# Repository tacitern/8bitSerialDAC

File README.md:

# 8bitSerialDAC
An 8-bit DAC which uses a Shift Register and R-2R Ladder

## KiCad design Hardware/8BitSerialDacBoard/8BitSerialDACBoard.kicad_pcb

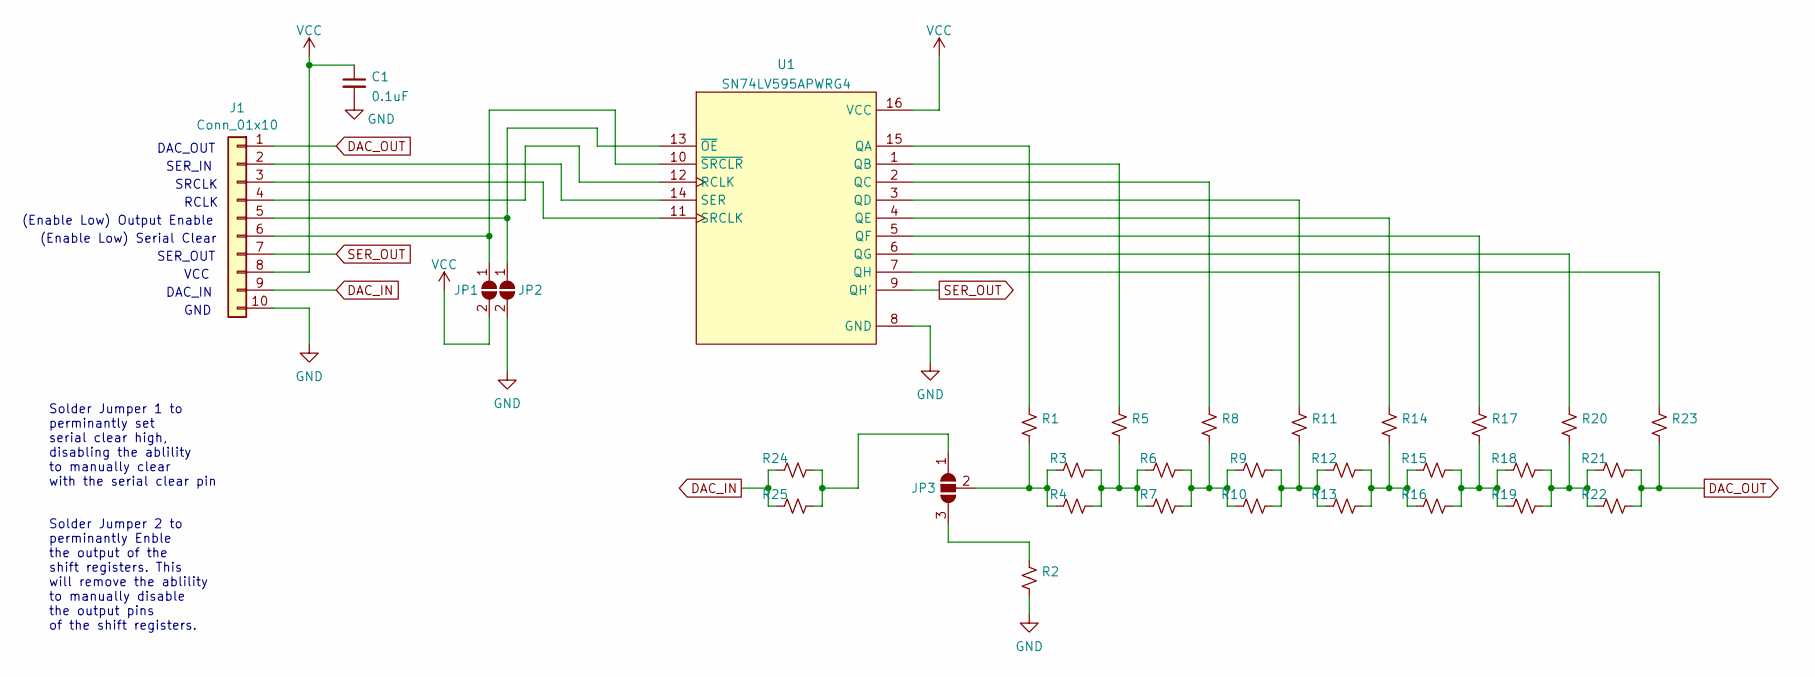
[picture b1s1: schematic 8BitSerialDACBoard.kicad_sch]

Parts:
C1: 0.1uF; C_0603_1608Metric_Pad1.08x0.95mm_HandSolder
J1: Conn_01x10; PinHeader_1x10_P2.54mm_Vertical
JP1, JP2: SolderJumper_2_Open; SolderJumper-2_P1.3mm_Open_TrianglePad1.0x1.5mm
JP3: SolderJumper_3_Open; SolderJumper-3_P1.3mm_Open_RoundedPad1.0x1.5mm
R1, R2, R3, R4, R5, R6, R7, R8, R9, R10, R11, R12, R13, R14, R15, R16, R17, R18, R19, R20, R21, R22, R23, R24, R25: R_Small_US; R_0603_1608Metric_Pad0.98x0.95mm_HandSolder
U1: SN74LV595APWRG4

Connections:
DAC_IN: J1.9, R24.1, R25.1
DAC_OUT: J1.1, R21.2, R22.2, R23.2
GND: C1.2, J1.10, JP2.2 (B), R2.2, U1.8 (GND)
unnamed: J1.2, U1.14 (SER)
unnamed: J1.3, U1.11 (SRCLK)
unnamed: J1.4, U1.12 (RCLK)
unnamed: J1.5, JP2.1 (A), U1.13 (~OE)
unnamed: J1.6, JP1.1 (A), U1.10 (~SRCLR)
unnamed: JP3.1 (A), R24.2, R25.2
unnamed: JP3.3 (B), R2.1
unnamed: JP3.2 (C), R1.2, R3.1, R4.1
unnamed: R3.2, R4.2, R5.2, R6.1, R7.1
unnamed: R6.2, R7.2, R8.2, R9.1, R10.1
unnamed: R9.2, R10.2, R11.2, R12.1, R13.1
unnamed: R12.2, R13.2, R14.2, R15.1, R16.1
unnamed: R15.2, R16.2, R17.2, R18.1, R19.1
unnamed: R18.2, R19.2, R20.2, R21.1, R22.1
unnamed: R1.1, U1.15 (QA)
unnamed: R5.1, U1.1 (QB)
unnamed: R8.1, U1.2 (QC)
unnamed: R11.1, U1.3 (QD)
unnamed: R14.1, U1.4 (QE)
unnamed: R17.1, U1.5 (QF)
unnamed: R20.1, U1.6 (QG)
unnamed: R23.1, U1.7 (QH)
SER_OUT: J1.7, U1.9 (QH')
VCC: C1.1, J1.8, JP1.2 (B), U1.16 (VCC)

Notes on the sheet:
Solder Jumper 2 to perminantly Enble the output of the shift registers. This will remove the ablility to manually disable the output pins of the shift registers.
SER_IN
SER_OUT
RCLK
Solder Jumper 1 to perminantly set serial clear high, disabling the ablility to manually clear with the serial clear pin
DAC_IN
VCC
(Enable Low) Serial Clear
GND
DAC_OUT
SRCLK
(Enable Low) Output Enable

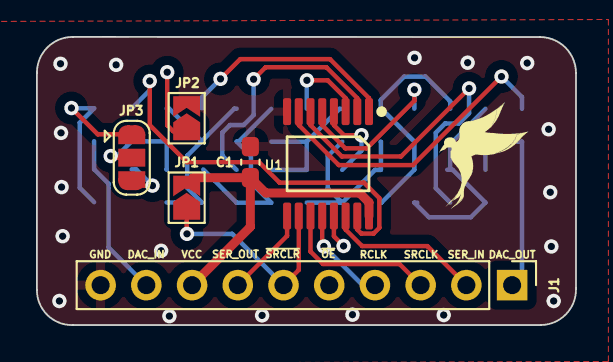
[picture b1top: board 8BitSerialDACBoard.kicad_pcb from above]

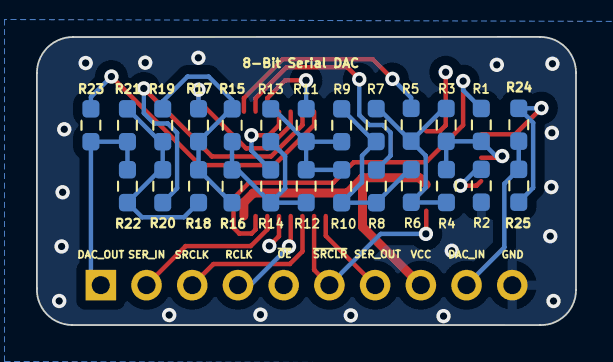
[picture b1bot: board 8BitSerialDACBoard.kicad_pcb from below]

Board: 4 copper layers, 29.9 x 16.0 mm, 31 parts (25 on the bottom side), 27 nets.

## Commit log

2023-12-03 First pass at a PCB for an 8bit IO expanded R-2R ladder DAC
2023-12-20 Adding chainablity to DACs, need to flip bit direction
